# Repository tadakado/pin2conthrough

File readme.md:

#  pin2conthroughとは

Pro MicroやBLE Micro Proなどをブレッドボードでテストする際に、[マックエイト社のコンスルー](https://www.mac8sdk.co.jp/products/217)を使えるようにする変換基板です。自作キーボードなどで用いるマイコンボードにピンヘッダを取り付けずに利用できます。

変換基板は2列x13ピン構成でとなっています。マイコンボード用のスルーホール列の間隔は15.24mm(2.54x6)です。ブレッドボード用のスルーホール列は内側にあり、ブレッドボードが有効に使えます。スルーホール径は0.85mm(設計値)です。ピンヘッダは[秋月電子の細ピンヘッダ](https://akizukidenshi.com/catalog/g/gC-04397/)を使用します。また、[SOT-23-5タイプのレギュレータ](https://akizukidenshi.com/catalog/g/gI-10675/)を実装できるようになっています。ハンダジャンパによって26ピンに出力が可能です。入力は24と25からGNDとVCCを利用します。例えばBLE Micro Proの場合、このピンにコンスルーを使わないことで、ブレッドボードで3.3Vや1.8Vを電源として用意できます。レギュレータとコンデンサは付いていませんので、別途ご用意ください。

面付した基板で製造しているため、バリが残っています。使用の際はダイヤモンドやすりなどで整形したうえでご使用ください。ダイヤモンドやすりは100均ショップのもので十分です。

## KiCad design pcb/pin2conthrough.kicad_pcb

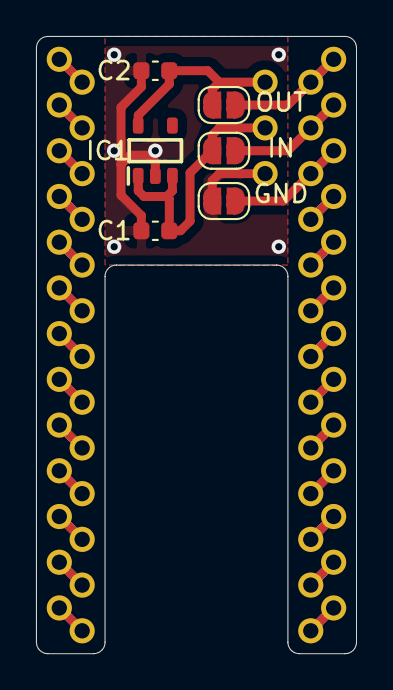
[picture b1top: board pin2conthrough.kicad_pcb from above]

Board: 2 copper layers, 17.8 x 34.3 mm, 11 parts (0 on the bottom side), 29 nets.

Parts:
C1, C2: C; C_0603_1608Metric
IC1: NJM12888F18-TE1; SOT95P280X130-5N
J1, J2, J3, J4: Conn_01x13; PinHeader_1x13_P2.54mm_Vertical
J5: Conn_01x03; PinHeader_1x03_P2.54mm_Vertical
JP1, JP2, JP3: Jumper_NO_Small; SolderJumper-2_P1.3mm_Open_RoundedPad1.0x1.5mm

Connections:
GND: C1.2, C2.2, IC1.2, J5.3, JP3.1
unnamed: C1.1, IC1.1, IC1.3, J5.2, JP2.1
unnamed: C2.1, IC1.5, J5.1, JP1.1
unnamed: J1.1, J2.1
unnamed: J1.2, J2.2
unnamed: J1.3, J2.3
unnamed: J1.4, J2.4
unnamed: J1.5, J2.5
unnamed: J1.6, J2.6
unnamed: J1.7, J2.7
unnamed: J1.8, J2.8
unnamed: J1.9, J2.9
unnamed: J1.10, J2.10
unnamed: J1.11, J2.11
unnamed: J1.12, J2.12
unnamed: J1.13, J2.13
unnamed: J3.1, J4.1, JP1.2
unnamed: J3.2, J4.2, JP2.2
unnamed: J3.3, J4.3, JP3.2
unnamed: J3.4, J4.4
unnamed: J3.5, J4.5
unnamed: J3.6, J4.6
unnamed: J3.7, J4.7
unnamed: J3.8, J4.8
unnamed: J3.9, J4.9
unnamed: J3.10, J4.10
unnamed: J3.11, J4.11
unnamed: J3.12, J4.12
unnamed: J3.13, J4.13

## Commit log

2022-05-04 initial
